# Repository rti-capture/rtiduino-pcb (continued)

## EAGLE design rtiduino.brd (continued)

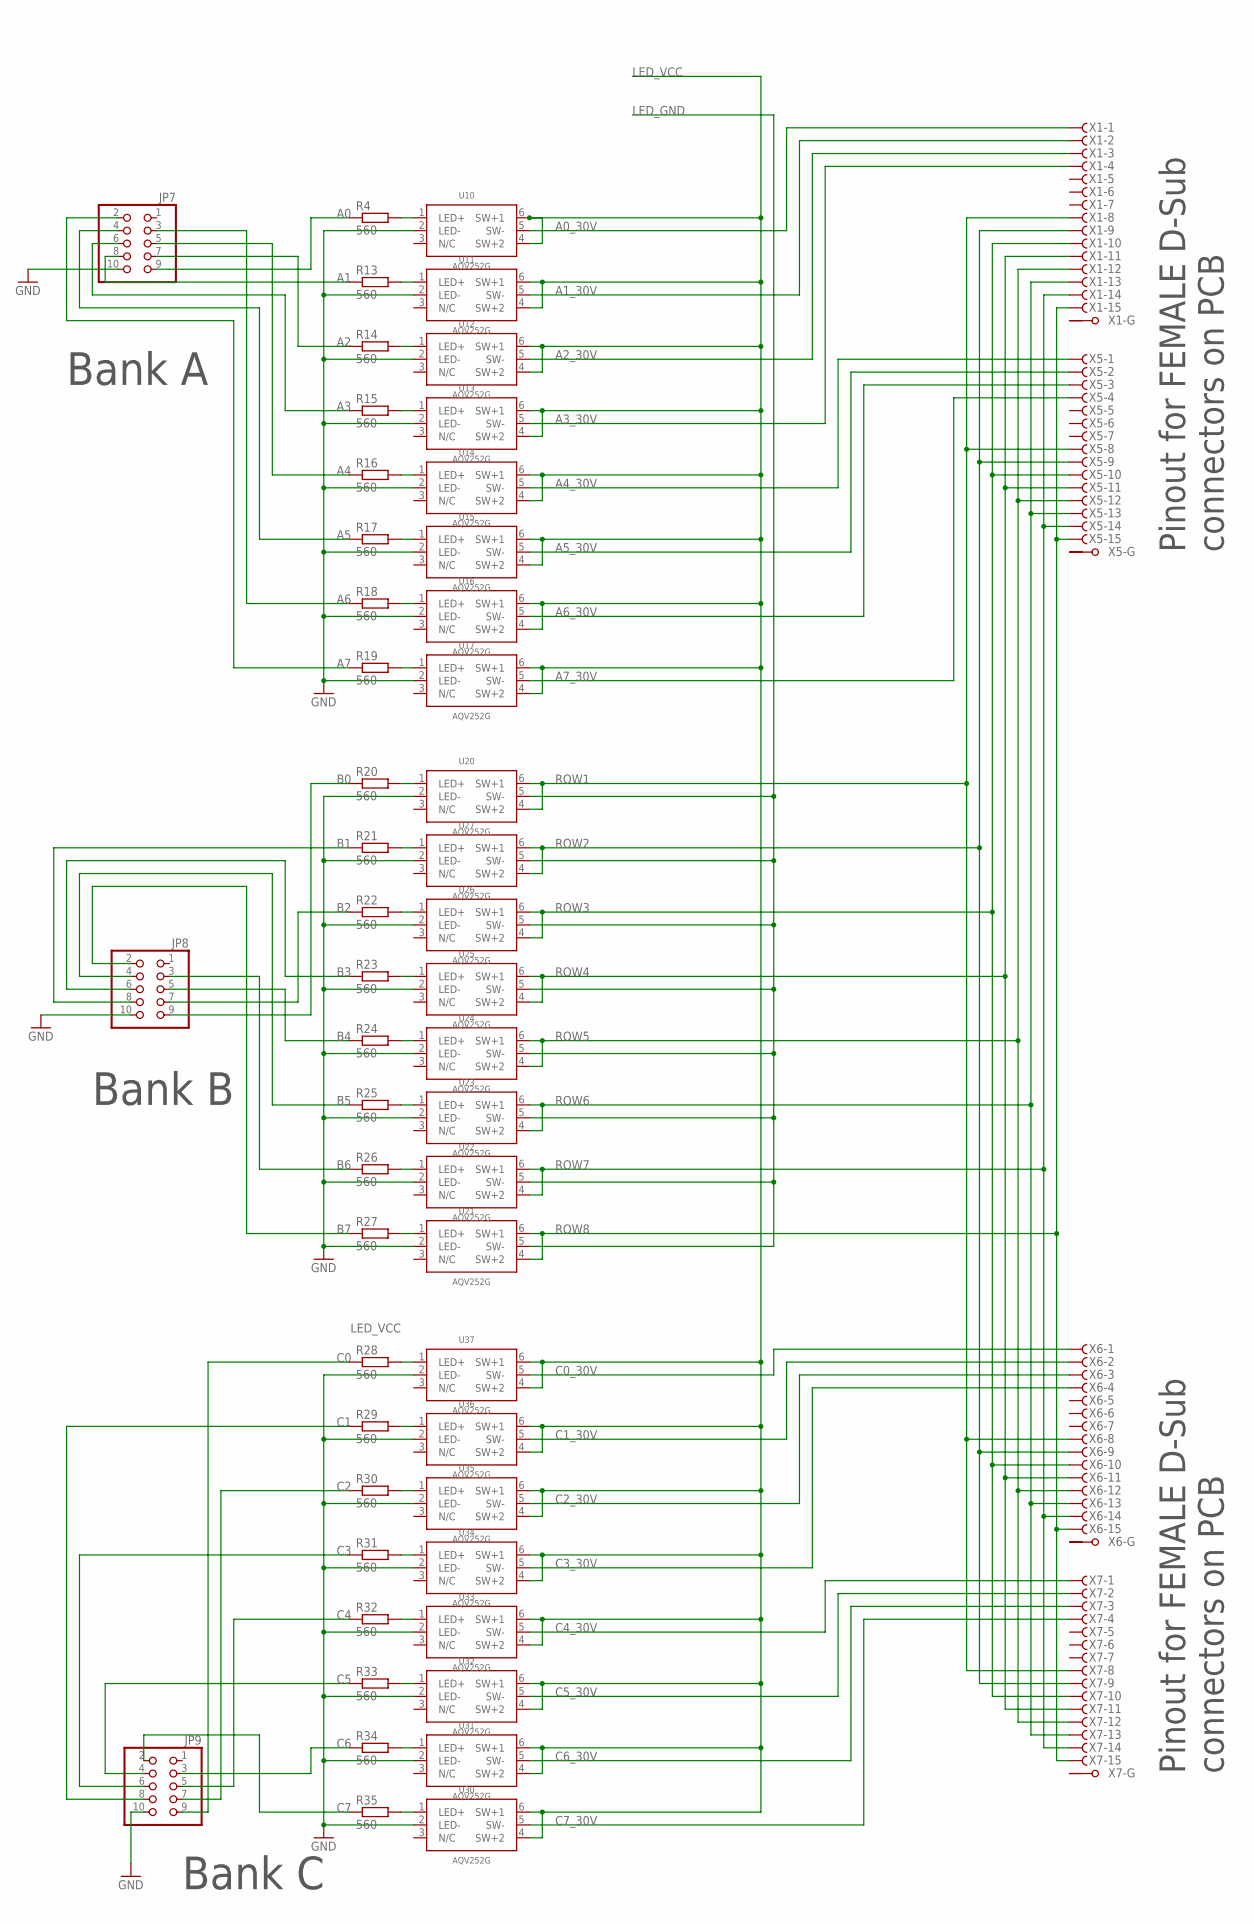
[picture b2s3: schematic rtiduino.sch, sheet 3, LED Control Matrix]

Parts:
JP7, JP8, JP9: PINHD-2X5; 2X05
R4, R13, R14, R15, R16, R17, R18, R19, R20, R21, R22, R23, R24, R25, R26, R27, R28, R29, R30, R31, R32, R33, R34, R35: 560; R0805
U10, U11, U12, U13, U14, U15, U16, U17, U20, U21, U22, U23, U24, U25, U26, U27, U30, U31, U32, U33, U34, U35, U36, U37: AQV252G; SOP6
X1, X5, X6, X7: F15HPS; F15HP

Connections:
A0: JP7.9, R4.1; also elsewhere on the board
A0_30V: U10.5 (SW-), X1.1 (F)
A1: JP7.8, R13.1; also elsewhere on the board
A1_30V: U11.5 (SW-), X1.2 (F)
A2: JP7.7, R14.1; also elsewhere on the board
A2_30V: U12.5 (SW-), X1.3 (F)
A3: JP7.6, R15.1; also elsewhere on the board
A3_30V: U13.5 (SW-), X1.4 (F)
A4: JP7.5, R16.1; also elsewhere on the board
A4_30V: U14.5 (SW-), X5.1 (F)
A5: JP7.4, R17.1; also elsewhere on the board
A5_30V: U15.5 (SW-), X5.2 (F)
A6: JP7.3, R18.1; also elsewhere on the board
A6_30V: U16.5 (SW-), X5.3 (F)
A7: JP7.2, R19.1; also elsewhere on the board
A7_30V: U17.5 (SW-), X5.4 (F)
B0: JP8.9, R20.1; also elsewhere on the board
B1: JP8.8, R21.1; also elsewhere on the board
B2: JP8.7, R22.1; also elsewhere on the board
B3: JP8.6, R23.1; also elsewhere on the board
B4: JP8.5, R24.1; also elsewhere on the board
B5: JP8.4, R25.1; also elsewhere on the board
B6: JP8.3, R26.1; also elsewhere on the board
B7: JP8.2, R27.1; also elsewhere on the board
C0: JP9.9, R28.1; also elsewhere on the board
C0_30V: U37.5 (SW-), X6.1 (F)
C1: JP9.8, R29.1; also elsewhere on the board
C1_30V: U36.5 (SW-), X6.2 (F)
C2: JP9.7, R30.1; also elsewhere on the board
C2_30V: U35.5 (SW-), X6.3 (F)
C3: JP9.6, R31.1; also elsewhere on the board
C3_30V: U34.5 (SW-), X6.4 (F)
C4: JP9.5, R32.1; also elsewhere on the board
C4_30V: U33.5 (SW-), X7.1 (F)
C5: JP9.4, R33.1; also elsewhere on the board
C5_30V: U32.5 (SW-), X7.2 (F)
C6: JP9.3, R34.1; also elsewhere on the board
C6_30V: U31.5 (SW-), X7.3 (F)
C7: JP9.2, R35.1; also elsewhere on the board
C7_30V: U30.5 (SW-), X7.4 (F)
GND: JP7.10, JP8.10, JP9.10, U10.2 (LED-), U11.2 (LED-), U12.2 (LED-), U13.2 (LED-), U14.2 (LED-), U15.2 (LED-), U16.2 (LED-), U17.2 (LED-), U20.2 (LED-), U21.2 (LED-), U22.2 (LED-), U23.2 (LED-), U24.2 (LED-), U25.2 (LED-), U26.2 (LED-), U27.2 (LED-), U30.2 (LED-), U31.2 (LED-), U32.2 (LED-), U33.2 (LED-), U34.2 (LED-), U35.2 (LED-), U36.2 (LED-), U37.2 (LED-); also elsewhere on the board
LED_GND: U20.5 (SW-), U21.5 (SW-), U22.5 (SW-), U23.5 (SW-), U24.5 (SW-), U25.5 (SW-), U26.5 (SW-), U27.5 (SW-); also elsewhere on the board
LED_VCC: U10.4 (SW+2), U10.6 (SW+1), U11.4 (SW+2), U11.6 (SW+1), U12.4 (SW+2), U12.6 (SW+1), U13.4 (SW+2), U13.6 (SW+1), U14.4 (SW+2), U14.6 (SW+1), U15.4 (SW+2), U15.6 (SW+1), U16.4 (SW+2), U16.6 (SW+1), U17.4 (SW+2), U17.6 (SW+1), U30.4 (SW+2), U30.6 (SW+1), U31.4 (SW+2), U31.6 (SW+1), U32.4 (SW+2), U32.6 (SW+1), U33.4 (SW+2), U33.6 (SW+1), U34.4 (SW+2), U34.6 (SW+1), U35.4 (SW+2), U35.6 (SW+1), U36.4 (SW+2), U36.6 (SW+1), U37.4 (SW+2), U37.6 (SW+1); also elsewhere on the board
unnamed: R4.2, U10.1 (LED+)
unnamed: R14.2, U12.1 (LED+)
unnamed: R15.2, U13.1 (LED+)
unnamed: R18.2, U16.1 (LED+)
unnamed: R16.2, U14.1 (LED+)
unnamed: R17.2, U15.1 (LED+)
unnamed: R13.2, U11.1 (LED+)
unnamed: R19.2, U17.1 (LED+)
unnamed: R28.2, U37.1 (LED+)
unnamed: R29.2, U36.1 (LED+)
unnamed: R30.2, U35.1 (LED+)
unnamed: R31.2, U34.1 (LED+)
unnamed: R32.2, U33.1 (LED+)
unnamed: R33.2, U32.1 (LED+)
unnamed: R34.2, U31.1 (LED+)
unnamed: R35.2, U30.1 (LED+)
unnamed: R20.2, U20.1 (LED+)
unnamed: R21.2, U27.1 (LED+)
unnamed: R22.2, U26.1 (LED+)
unnamed: R23.2, U25.1 (LED+)
unnamed: R24.2, U24.1 (LED+)
unnamed: R25.2, U23.1 (LED+)
unnamed: R26.2, U22.1 (LED+)
unnamed: R27.2, U21.1 (LED+)
ROW1: U20.4 (SW+2), U20.6 (SW+1), X1.8 (F), X5.8 (F), X6.8 (F), X7.8 (F)
ROW2: U27.4 (SW+2), U27.6 (SW+1), X1.9 (F), X5.9 (F), X6.9 (F), X7.9 (F)
ROW3: U26.4 (SW+2), U26.6 (SW+1), X1.10 (F), X5.10 (F), X6.10 (F), X7.10 (F)
ROW4: U25.4 (SW+2), U25.6 (SW+1), X1.11 (F), X5.11 (F), X6.11 (F), X7.11 (F)
ROW5: U24.4 (SW+2), U24.6 (SW+1), X1.12 (F), X5.12 (F), X6.12 (F), X7.12 (F)
ROW6: U23.4 (SW+2), U23.6 (SW+1), X1.13 (F), X5.13 (F), X6.13 (F), X7.13 (F)
ROW7: U22.4 (SW+2), U22.6 (SW+1), X1.14 (F), X5.14 (F), X6.14 (F), X7.14 (F)
ROW8: U21.4 (SW+2), U21.6 (SW+1), X1.15 (F), X5.15 (F), X6.15 (F), X7.15 (F)

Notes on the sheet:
Pinout for FEMALE D-Sub connectors on PCB
Bank A
Bank B
Bank C

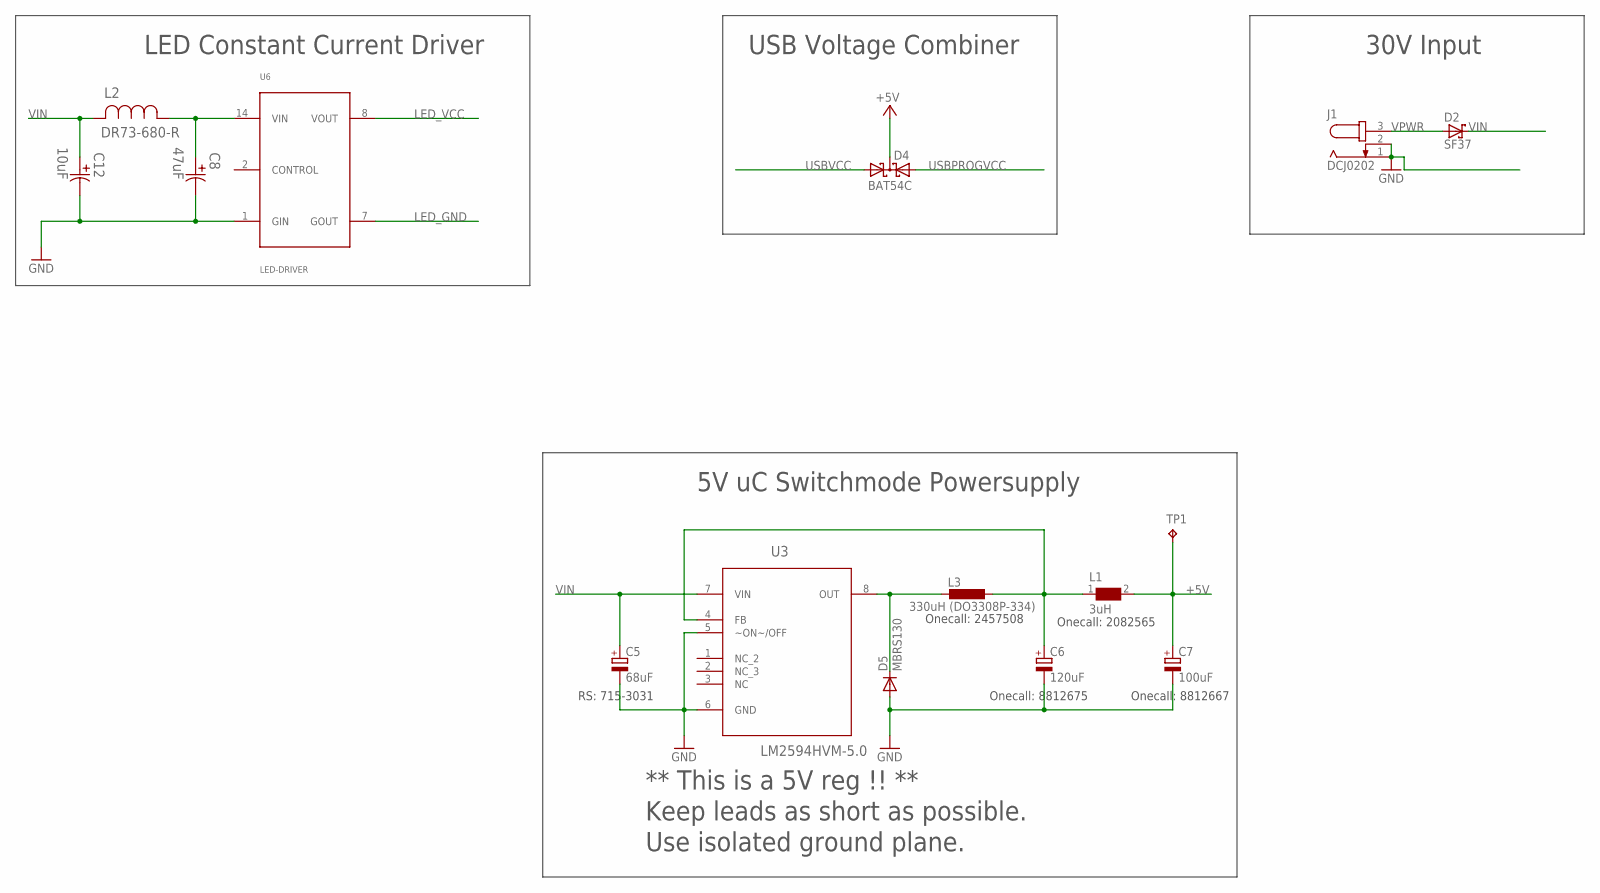
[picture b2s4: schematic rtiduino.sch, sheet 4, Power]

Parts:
C5: 68uF; E5-13
C6: 120uF; E5-13
C7: 100uF; E5-13
C8: 47uF; CAPAE830X1050N
C12: 10uF; CAPAE660X610N
D2: SF37; DO-201AD
D4: BAT54C; SOT23
D5: MBRS130; DO214AA
J1: DCJ0202; SPC4077
L1: 3uH; WE-TPC_5818/5828
L2: DR73-680-R; INDM7676X355N
L3: 330uH (DO3308P-334); DO3316P
TP1: TPB2,54; B2,54
U3: LM2594HVM-5.0; SOIC127P620X175-8N
U6: LED-DRIVER; LDU08

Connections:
+5V: C7.+, D4.3 (CC), L1.2, TP1.TP; also elsewhere on the board
GND: C5.-, C6.-, C7.-, C8.2, C12.2, D5.A, J1.1, J1.2, U3.5 (~ON~/OFF), U3.6 (GND), U6.1 (GIN); also elsewhere on the board
LED_GND: U6.7 (GOUT); also elsewhere on the board
LED_VCC: U6.8 (VOUT); also elsewhere on the board
unnamed: C6.+, L1.1, L3.2, U3.4 (FB)
unnamed: C8.1, L2.1, U6.14 (VIN)
unnamed: D5.C, L3.1, U3.8 (OUT)
USBPROGVCC: D4.2 (A2); also elsewhere on the board
USBVCC: D4.1 (A1); also elsewhere on the board
VIN: C5.+, C12.1, D2.1 (C), L2.2, U3.7 (VIN)
VPWR: D2.2 (A), J1.3

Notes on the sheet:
LED Constant Current Driver
USB Voltage Combiner
30V Input
** This is a 5V reg !! ** Keep leads as short as possible. Use isolated ground plane.
Onecall: 2457508
Onecall: 8812675
RS: 715-3031
Onecall: 8812667
Onecall: 2082565
5V uC Switchmode Powersupply

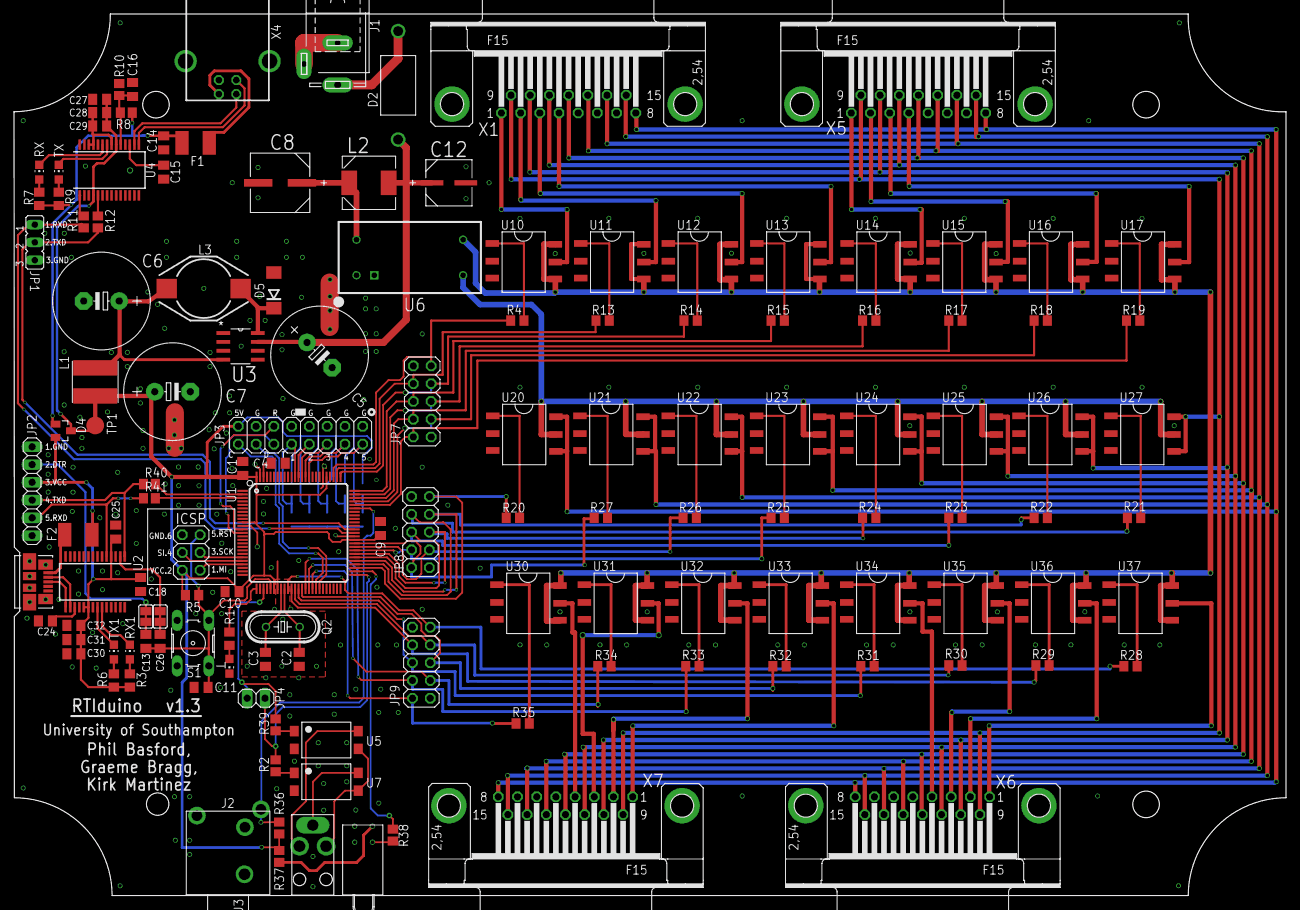
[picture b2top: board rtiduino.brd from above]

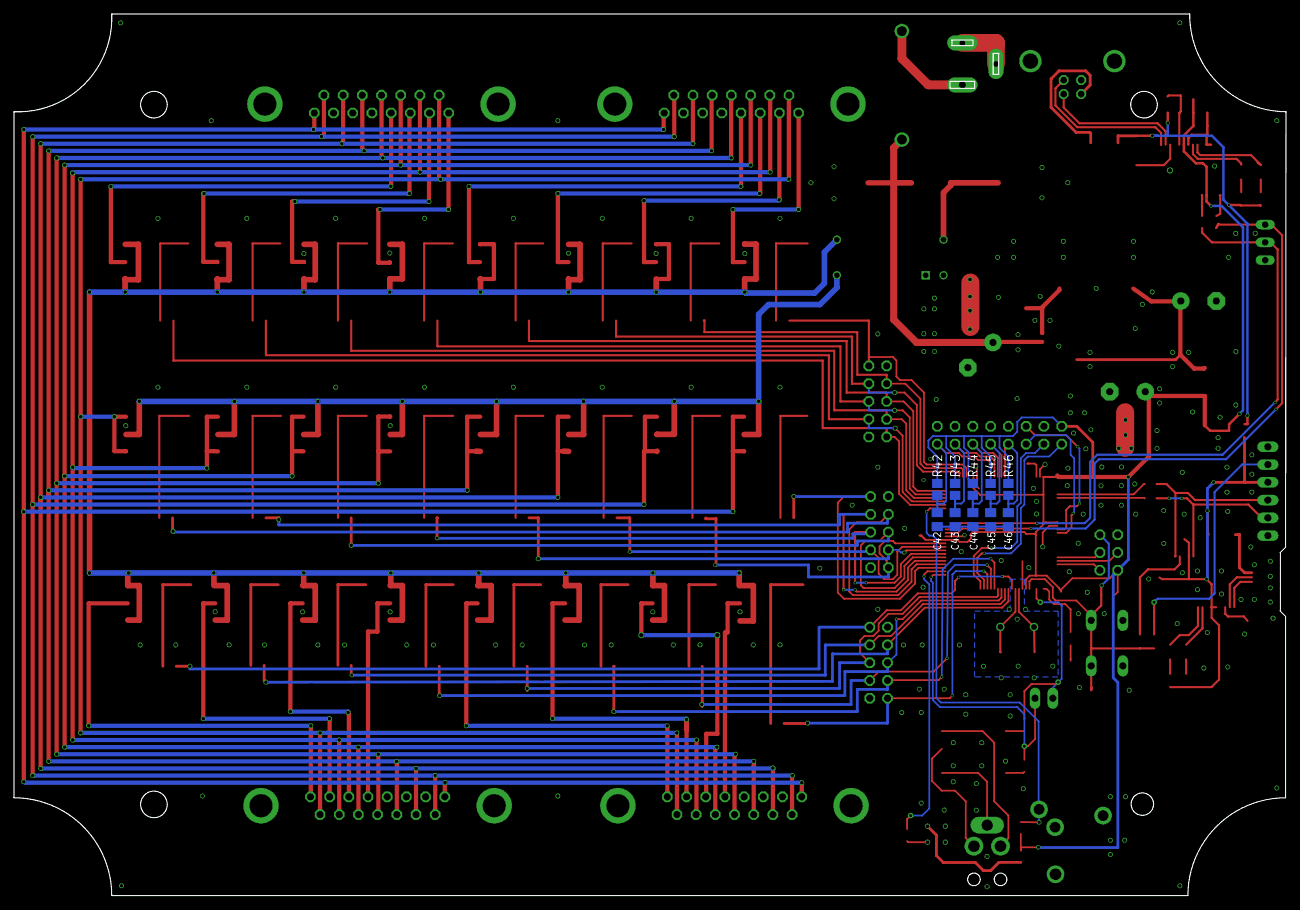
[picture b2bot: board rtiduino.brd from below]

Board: 2 copper layers, 181.8 x 126.0 mm, 144 parts (10 on the bottom side), 139 nets.

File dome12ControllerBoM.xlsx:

Qty | Value | Device | Package | Parts | Description | CURRENTRATING | INDUCTANCE | MF | MPN | OC_FARNELL | OC_NEWARK | PACKAGE | SUPPLIER | TOLERANCE | TP_SIGNAL_NAME | VALUE | VOLTAGERATING
1 |  | 10-XX | B3F-10XX | S1 | OMRON SWITCH
4 |  | F15HPS | F15HP | X1, X5, X6, X7 | SUB-D
1 |  | JP2E | JP2 | JP1 | JUMPER
5 |  | LED0805ROUND | 0805RND | L, RX, RX1, TX, TX1 | LED
1 |  | PINHD-1X6 | 1X06 | JP2 | PIN HEADER
3 |  | PINHD-2X5 | 2X05 | JP7, JP8, JP9 | PIN HEADER
1 |  | PINHD-2X8 | 2X08 | JP3 | PIN HEADER
1 |  | PN61729 | PN61729 | X4 | BERG USB connector
1 |  | SJ | SJ | RESET-EN | SMD solder JUMPER
12 | 100n | C-EUC0805K | C0805K | C1, C4, C9, C10, C14, C15, C16, C42, C43, C44, C45, C46 | CAPACITOR, European symbol
8 | 100nF | C-EUC0805K | C0805K | C18, C24, C25, C26, C27, C28, C30, C31 | CAPACITOR, European symbol
1 | 100uF | CPOL-EUE5-13 | E5-13 | C7 | POLARIZED CAPACITOR, European symbol
3 | 10K | R-EU_R0805 | R0805 | R5, R10, R36 | RESISTOR, European symbol
1 | 10UF | EEE-FK1J100P-CASE-D | CAPAE660X610N | C12 | Aluminum Electrolytic Capacitors,Surface Mount Type |  |  |  | EEE-FK1J100P | 9696008 | 96K9398 | CASE-D | PANASONIC | ｱ20 % |  | 10UF | 63 V
5 | 10k | R-EU_R0805 | R0805 | R42, R43, R44, R45, R46 | RESISTOR, European symbol
1 | 120uF | CPOL-EUE5-13 | E5-13 | C6 | POLARIZED CAPACITOR, European symbol
1 | 122-000-04-52 | 122-000-04-52 | 122-000-04-52 | U$28
1 | 16MHz | CRYTALHC49S | HC49/S | Q2 | CRYSTAL
5 | 1K | R-EU_R0805 | R0805 | R1, R11, R12, R40, R41 | RESISTOR, European symbol
4 | 1k | R-EU_R0805 | R0805 | R3, R6, R7, R9 | RESISTOR, European symbol
1 | 2.5MM-JACKPRO | 2.5MM-JACKPRO | 2.5-JACK-RA-PRO | J3
3 | 22p | C-EUC0805K | C0805K | C2, C3, C11 | CAPACITOR, European symbol
1 | 3.5MM-JACK | 3.5MM-JACK | 3.5-JACK-RA | J2
1 | 330uH (DO3308P-334) | DO3316P | DO3316P | L3 | COILCRAFT |  |  |  |  | unknown | unknown
1 | 3uH | WE-TPC-744053003_5818/5828 | WE-TPC_5818/5828 | L1 | Shielded Tiny Power Inductor WE-TPC |  |  |  | 744053003 | 2082565 | 88T7010 | 5828 | WURTH ELEKTRONIK
2 | 4.7uF | C-EUC0805K | C0805K | C29, C32 | CAPACITOR, European symbol
1 | 47UF | EEE-FK1J470P-CASE-F | CAPAE830X1050N | C8 | Aluminum Electrolytic Capacitors,Surface Mount Type |  |  |  | EEE-FK1J470P | 9696032 | 96K9403 | CASE-F | PANASONIC | ｱ20 % |  | 47UF | 63 V
1 | 4K7 | R-EU_R0805 | R0805 | R8 | RESISTOR, European symbol
2 | 500mA | L-EUL1812 | L1812 | F1, F2 | INDUCTOR, European symbol
27 | 560 | R-EU_R0805 | R0805 | R4, R13, R14, R15, R16, R17, R18, R19, R20, R21, R22, R23, R24, R25, R26, R27, 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 | RESISTOR, European symbol
1 | 68uF | CPOL-EUE5-13 | E5-13 | C5 | POLARIZED CAPACITOR, European symbol
24 | AQV252G | AQV252G | SOP6 | U10, U11, U12, U13, U14, U15, U16, U17, U20, U21, U22, U23, U24, U25, U26, U27,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
1 | ATMEGA2560AU | ATMEGA2560AU | TQFP100 | U1 | MICROCONTROLLER
1 | BAT54C | BAT54C | SOT23 | D4 | Schottky Diodes
1 | DCJ0202 | JACK-PLUG0 | SPC4077 | J1 | DC POWER JACK |  |  |  |  | unknown | unknown
1 | DR73-680-R | DR73-680-R | INDM7676X355N | L2 | POWER INDUCTOR | 890mA | 68ｵH |  | DR73-680-R | 1653721 | 52K7562 | SMD | COILTRONICS | ｱ20%
1 | FOD852 | FOD852 | DIP4-SMD | U5
2 | FT232RL | FT232RL | SSOP28 | U2, U4
1 | ICSP | PINHD-2X3 | 2X03 | ICSP | PIN HEADER
1 | LED-DRIVER | LED-DRIVER | LDU08 | U6
1 | LM2594HVM-5.0 | LM2594HVM-3.3 | SOIC127P620X175-8N | U3 | SIMPLE SWITCHER |  |  |  | LM2594HVM-33 | 1564635 | 41K3809 | SOIC-8 | National Semiconductor
1 | MBRS130 | DIODE-DO214AA | DO214AA | D5 | DIODE
1 | SF37 | SF37 | DO-201AD | D2
1 | TPB2,54 | TPB2,54 | B2,54 | TP1 | Test pad
1 | USB PROG | 47346-0001 | MOLEX_47346-0001 | J4 | CONN RCPT 5POS MICRO USB R/A SMD |  |  |  | 47346-0001 | 1568026 | 47M0505 | 5 POS MICRO USB R/A | MOLEX

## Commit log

2015-02-25 Libraries needed
2015-02-25 version 1.0
2015-02-25 Latest version with * fixed PSU arrangement * more caps * connectors moved outwards
2018-06-06 Update wih Superdome PCB
2018-06-06 BoM in excel format
2020-06-24 Fix footprints for 2.5mm jack and opto-isolator
2020-06-24 Tweak to camera shutter trigger (split focus and shutter), tweak to serial programming, misc fixes
2020-07-31 Version 1.3 of RTIDuino and updated order sheet
2020-07-31 First version of the tester PCB - need to finalise values
2020-08-04 Final tweaks before ordering
2020-08-04 Add production gerbers
2020-08-04 fix a SNAFU in the silkscree, unfortunately post production. Also added Eagle 9 CAMfor making these
